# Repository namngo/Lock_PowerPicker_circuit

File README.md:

# Lock_PowerPicker_circuit
A circuit to automatically pick between wall-adapter or battery for the electronic lock.

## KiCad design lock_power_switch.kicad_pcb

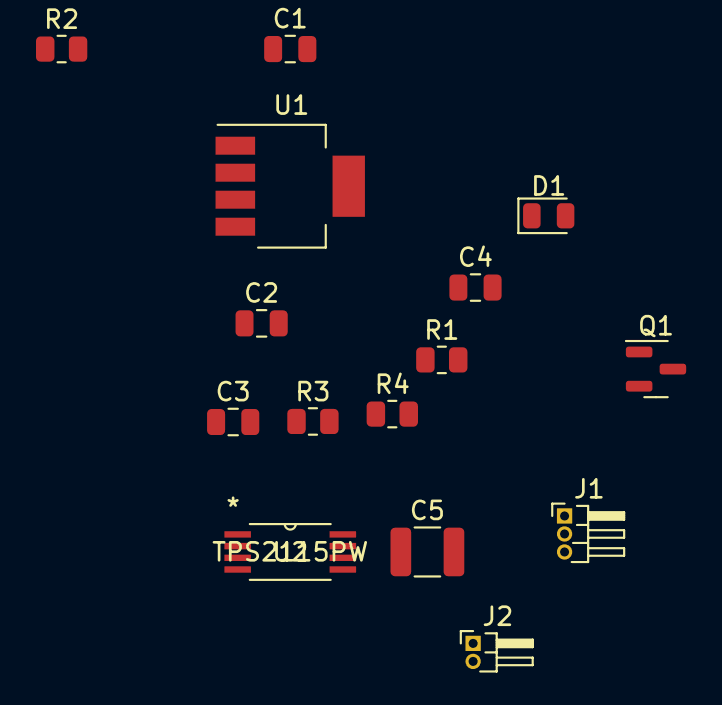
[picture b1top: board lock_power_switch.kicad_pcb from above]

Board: 2 copper layers, 15 parts (0 on the bottom side), 10 nets, no tracks yet.

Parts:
C1: 1uF; C_0805_2012Metric
C2: 1uf; C_0805_2012Metric
C3, C4: 0.1uf; C_0805_2012Metric
C5: 1uf; C_1210_3225Metric
D1: LED; LED_0805_2012Metric
J1: Supply_Conn; PinHeader_1x03_P1.00mm_Horizontal
J2: Lock_Conn; PinHeader_1x02_P1.00mm_Horizontal
Q1: Q_PMOS_GDS; SOT-23
R1: 50K; R_0805_2012Metric
R2: 1k; R_0805_2012Metric
R3: 100K; R_0805_2012Metric
R4: 150; R_0805_2012Metric
U1: LP38693MP-5.0; SOT-223-5
U2: TPS2115PW; TPS2115

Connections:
+BATT: C1.1, J2.2, R1.1, U1.4 (IN)
-BATT: C1.2, C2.2, C3.2, C4.2, C5.2, J1.2, R2.2, R4.2, U1.5 (GND), U2.2 (D0), U2.5 (GND)
unnamed: D1.1 (K), R4.1
unnamed: D1.2 (A), Q1.3 (S)
unnamed: Q1.1 (G), R3.1, U2.1 (STAT)
unnamed: R1.2, U1.1 (EN)
unnamed: R2.1, U2.4 (ILIM)
VAA: C3.1, J1.1, U2.3 (D1), U2.8 (IN1)
VCC: C2.1, C4.1, U1.3 (OUT), U2.6 (IN2)
lock+: C5.1, J2.1, Q1.2 (D), R3.2, U2.7 (OUT)

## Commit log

2022-10-25 initial kicad design
2022-10-25 half finish schematic
2022-10-26 finish schematic, moving to pcb
2022-10-27 ready to pcb
2022-10-27 remove kicad files
2022-10-27 add ealge files
2022-10-28 add the lp38693
2022-10-28 almost done
2022-10-28 finish sch
2022-10-30 finish the board
2022-10-30 ignore files
2022-10-30 done
2022-11-10 generate files
2023-01-02 finish chip version
2023-01-02 new board
2023-01-04 add back the driver
2023-01-06 finish board

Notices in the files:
parts and their libraries:
Copyright 2021 Accelerated Designs. All rights reserved.
